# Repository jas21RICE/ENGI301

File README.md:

# ENGI301
Repository for ENGI 301 course work

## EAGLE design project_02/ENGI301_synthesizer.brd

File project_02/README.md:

# project_2
Repository for files regarding the Pocket Synthesizer PCB. 
These files are for manufacturing a PCB for a Pocket Synthesizer using the BeagleBoard PocketBeagle.
The project details can be found here: https://www.hackster.io/jas21/pocketbeagle-synthesizer-10f638

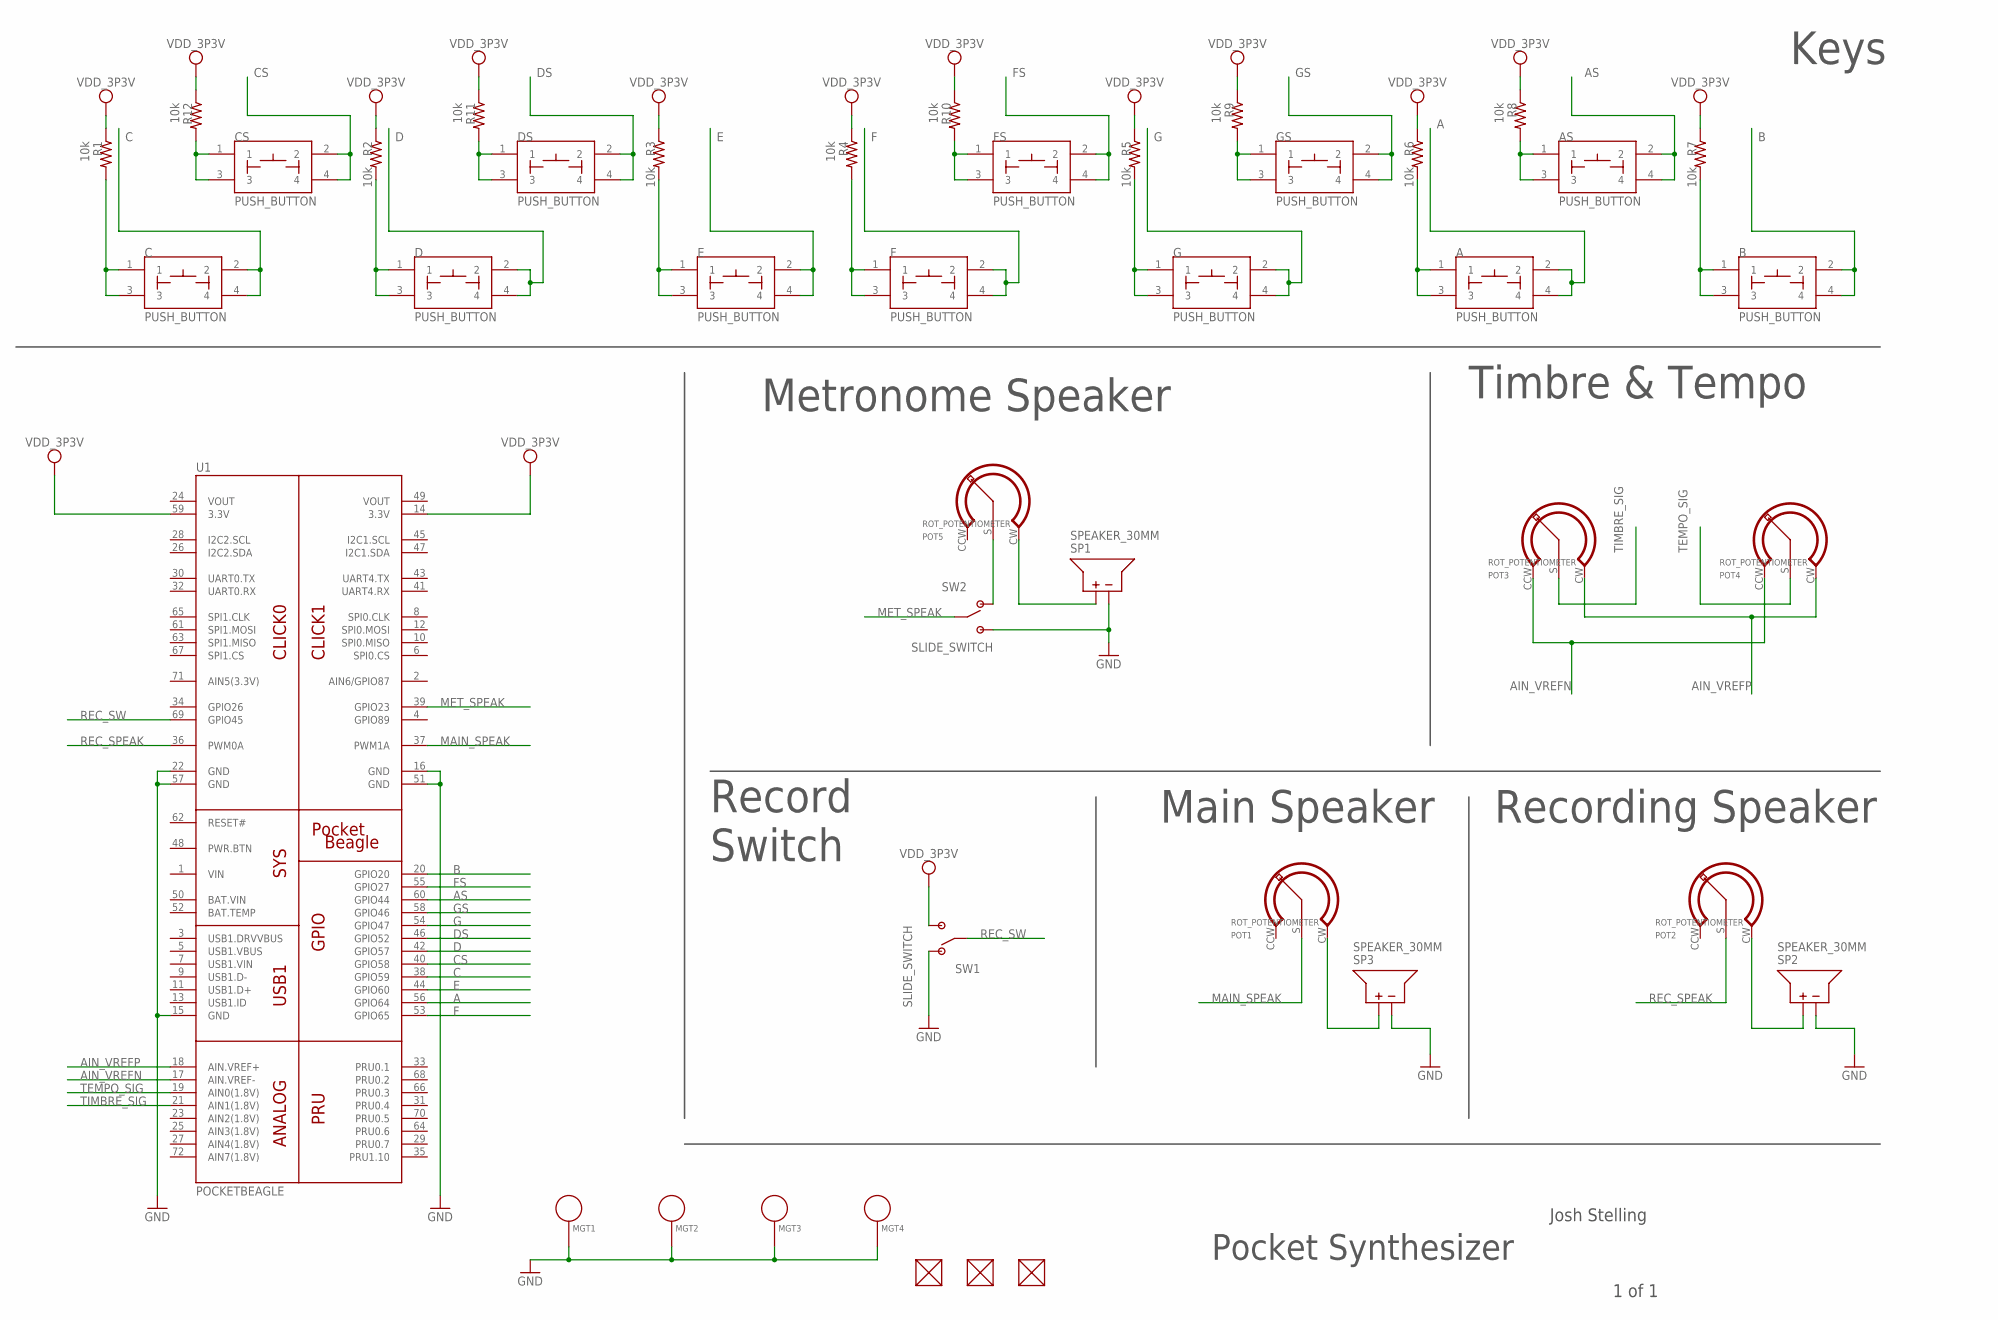
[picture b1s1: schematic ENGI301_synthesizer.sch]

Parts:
A: PUSH_BUTTON; BUTTON_12.5MM
AS: PUSH_BUTTON; BUTTON_12.5MM
B: PUSH_BUTTON; BUTTON_12.5MM
C: PUSH_BUTTON; BUTTON_12.5MM
CS: PUSH_BUTTON; BUTTON_12.5MM
D: PUSH_BUTTON; BUTTON_12.5MM
DS: PUSH_BUTTON; BUTTON_12.5MM
E: PUSH_BUTTON; BUTTON_12.5MM
F: PUSH_BUTTON; BUTTON_12.5MM
FS: PUSH_BUTTON; BUTTON_12.5MM
FUD1, FUD3, FUD4: FIDUCIAL; FIDUCIAL_40MIL
G: PUSH_BUTTON; BUTTON_12.5MM
GS: PUSH_BUTTON; BUTTON_12.5MM
MGT1, MGT2, MGT3, MGT4: MOUNTING_HOLE
POT1, POT2, POT3, POT4, POT5: ROT_POTENTIOMETER; POT-P102
R1, R2, R3, R4, R5, R6, R7, R8, R9, R10, R11, R12: 10k; R1210
SP1, SP2, SP3: SPEAKER_30MM
SW1, SW2: SLIDE_SWITCH; JS202011SCQN
U1: POCKETBEAGLE

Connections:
A: A.2, A.4, U1.56 (GPIO64)
AIN_VREFN: POT3.CCW, POT4.CCW, U1.17 (AIN.VREF-)
AIN_VREFP: POT3.CW, POT4.CW, U1.18 (AIN.VREF+)
AS: AS.2, AS.4, U1.60 (GPIO44)
B: B.2, B.4, U1.20 (GPIO20)
BAT.VIN: U1.50 (BAT.VIN)
C: C.2, C.4, U1.38 (GPIO59)
CS: CS.2, CS.4, U1.40 (GPIO58)
D: D.2, D.4, U1.42 (GPIO57)
DS: DS.2, DS.4, U1.46 (GPIO52)
E: E.2, E.4, U1.44 (GPIO60)
F: F.2, F.4, U1.53 (GPIO65)
FS: FS.2, FS.4, U1.55 (GPIO27)
G: G.2, G.4, U1.54 (GPIO47)
GND: MGT1.P$1, MGT2.P$1, MGT3.P$1, MGT4.P$1, SP1.-, SP2.-, SP3.-, SW1.1 (POS1), SW1.4 (POS1), SW2.3 (POS2), SW2.6 (POS2), U1.15 (GND), U1.16 (GND), U1.22 (GND), U1.51 (GND), U1.57 (GND)
GS: GS.2, GS.4, U1.58 (GPIO46)
MAIN_SPEAK: POT1.S (WIPER), U1.37 (PWM1A)
MET_SPEAK: SW2.2 (COMM), SW2.5 (COMM), U1.39 (GPIO23)
unnamed: C.1, C.3, R1.2
unnamed: D.1, D.3, R2.2
unnamed: POT5.CW, SP1.+
unnamed: POT5.S (WIPER), SW2.1 (POS1), SW2.4 (POS1)
unnamed: AS.1, AS.3, R8.2
unnamed: POT2.CW, SP2.+
unnamed: E.1, E.3, R3.2
unnamed: F.1, F.3, R4.2
unnamed: GS.1, GS.3, R9.2
unnamed: POT1.CW, SP3.+
unnamed: FS.1, FS.3, R10.2
unnamed: G.1, G.3, R5.2
unnamed: DS.1, DS.3, R11.2
unnamed: CS.1, CS.3, R12.2
unnamed: A.1, A.3, R6.2
unnamed: B.1, B.3, R7.2
REC_SPEAK: POT2.S (WIPER), U1.36 (PWM0A)
REC_SW: SW1.2 (COMM), SW1.5 (COMM), U1.69 (GPIO45)
TEMPO_SIG: POT4.S (WIPER), U1.19 (AIN0(1.8V))
TIMBRE_SIG: POT3.S (WIPER), U1.21 (AIN1(1.8V))
VDD_3P3V: R1.1, R2.1, R3.1, R4.1, R5.1, R6.1, R7.1, R8.1, R9.1, R10.1, R11.1, R12.1, SW1.3 (POS2), SW1.6 (POS2), U1.14 (3.3V), U1.59 (3.3V)
VIN: U1.1 (VIN)
VOUT: U1.24 (VOUT), U1.49 (VOUT)

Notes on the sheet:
Keys
Record Switch
Timbre & Tempo
Metronome Speaker
Main Speaker
Recording Speaker
Pocket Synthesizer
1 of 1
Josh Stelling

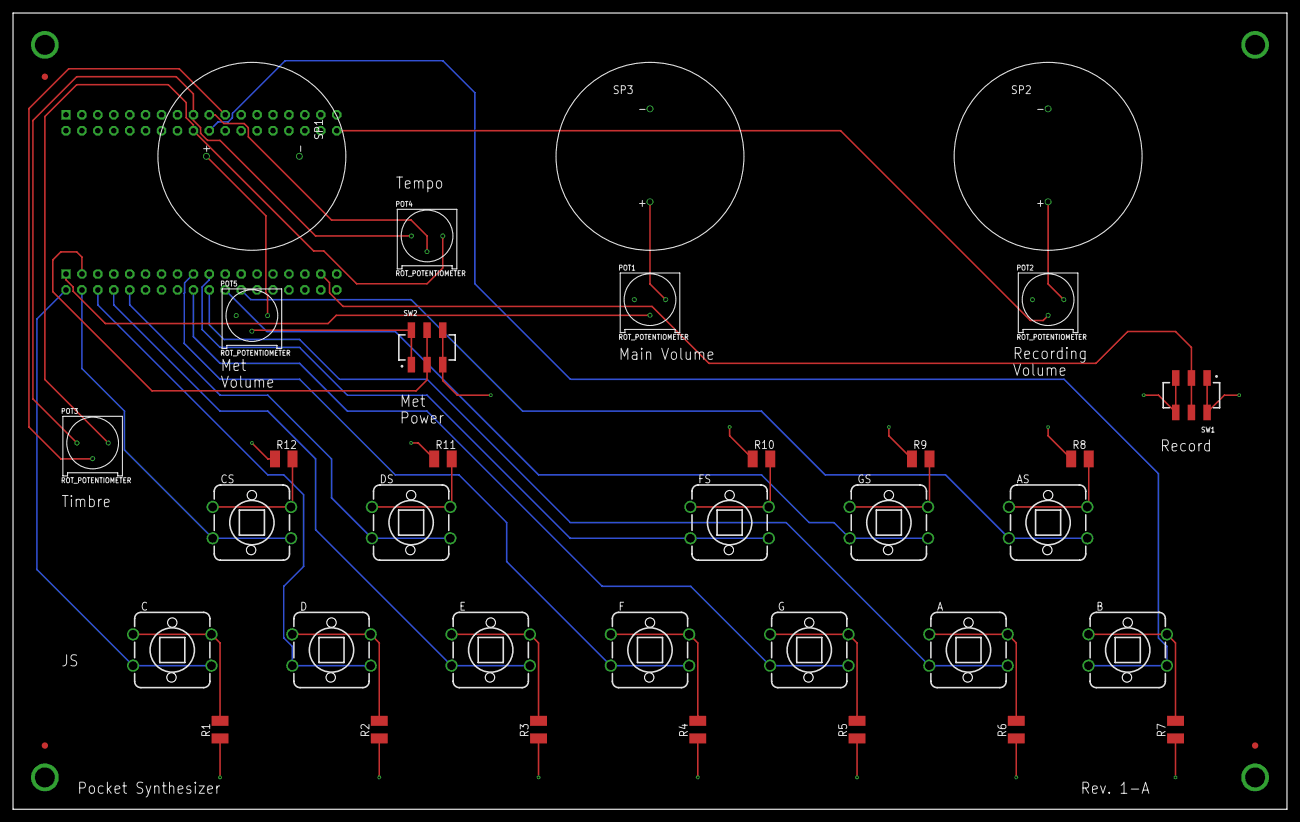
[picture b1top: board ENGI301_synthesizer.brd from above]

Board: 4 copper layers, 203.2 x 127.0 mm, 42 parts (1 on the bottom side), 39 nets.

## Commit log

2019-09-24 Updating README.md
2019-10-06 Adding simple calculator from in class
2019-10-06 Upgraded simple calculator to include left and right shift, modulo, and exponentiation.
2019-10-07 Created program to blink USR3 LED on PocketBeagle
2019-11-19 Updated with final project files
2019-11-27 PCB Project Proposal
2019-12-16 Uploading Schematic
2019-12-17 no message
2019-12-17 Made Board
